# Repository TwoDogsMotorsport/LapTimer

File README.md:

# INFRARED LAP TIMER FOR CIRCUIT RACING

## INTRODUCTION

This is far from an original idea, but that doesn't mean you shouldn't have a go.

We take part in private track days as well as club sprint races, where the result is based on individual lap times rather than track position.

The benefit here is that you can tailor this system to suit your needs.  Want to store more laps, add a bigger display allow downloads?  All these things are possible.

While this looks a fair bit like the AIM or Motec displays, it is not compatible with them, and if we've done our homework properly our system and theirs happily ignore each other.  If not, please raise an issue.

## CAN I BUILD THIS?

If you have some basic electronics skill and can work with hand tools, I think that's all you need.  I will leave the packaging up to you because everyone's needs are different, but it is pretty simple to get going

## SHOPPING LIST

### TRANSMITTER

* 1 x Arduino Nano
* 1 x 940nm Infra Red LED
* 1 x 180 ohm 1/4W resistor

For a longer range unit, you can use multiple LEDs and an N-Channel MOSFET to drive them  Look at https://learn.adafruit.com/rgb-led-strips/usage for an example.  The included schematic shows four LEDs using a MOSFET, but you could run more (or less) if you want.

### RECEIVER

* 1 x Arduino Nano
* 1 x TSOP382 (or equivalent) Infra Red Receiver module
* 1 x 4-line x 20 character LCD display

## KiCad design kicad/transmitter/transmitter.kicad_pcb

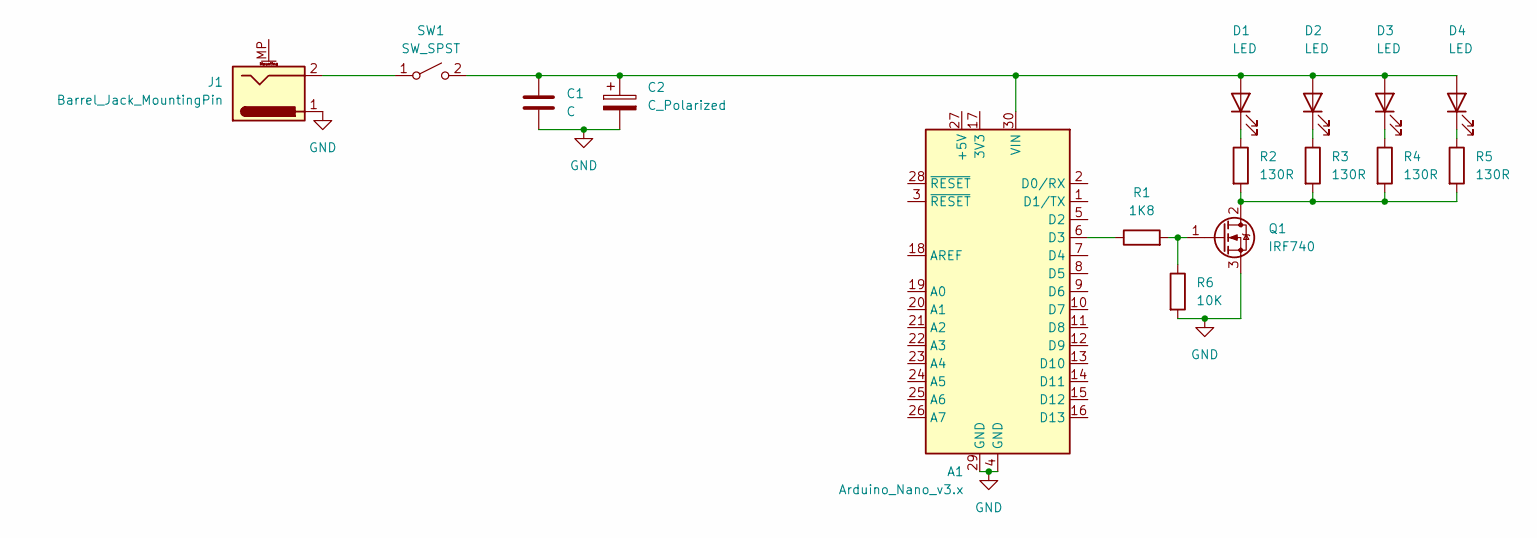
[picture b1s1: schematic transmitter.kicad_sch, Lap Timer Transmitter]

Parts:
A1: Arduino_Nano_v3.x; Arduino_Nano
C1: C; C_Disc_D4.7mm_W2.5mm_P5.00mm
C2: C_Polarized; CP_Radial_D10.0mm_P3.50mm
D1, D2, D3, D4: LED; LED_D5.0mm
J1: Barrel_Jack_MountingPin; BarrelJack_CUI_PJ-063AH_Horizontal
Q1: IRF740; TO-220-3_Vertical
R1: 1K8; R_Axial_DIN0207_L6.3mm_D2.5mm_P7.62mm_Horizontal
R2, R3, R4, R5: 130R; R_Axial_DIN0207_L6.3mm_D2.5mm_P7.62mm_Horizontal
R6: 10K; R_Axial_DIN0207_L6.3mm_D2.5mm_P7.62mm_Horizontal
SW1: SW_SPST; SW_Slide_SPDT_Straight_CK_OS102011MS2Q

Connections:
GND: A1.4 (GND), A1.29 (GND), C1.2, C2.2, J1.1, Q1.3 (S), R6.2
unnamed: A1.6 (D3), R1.1
unnamed: A1.30 (VIN), C1.1, C2.1, D1.2 (A), D2.2 (A), D3.2 (A), D4.2 (A), SW1.2 (B)
unnamed: D1.1 (K), R2.1
unnamed: D2.1 (K), R3.1
unnamed: D3.1 (K), R4.1
unnamed: D4.1 (K), R5.1
unnamed: Q1.2 (D), R2.2, R3.2, R4.2, R5.2
unnamed: Q1.1 (G), R1.2, R6.1
unnamed: J1.2, SW1.1 (A)

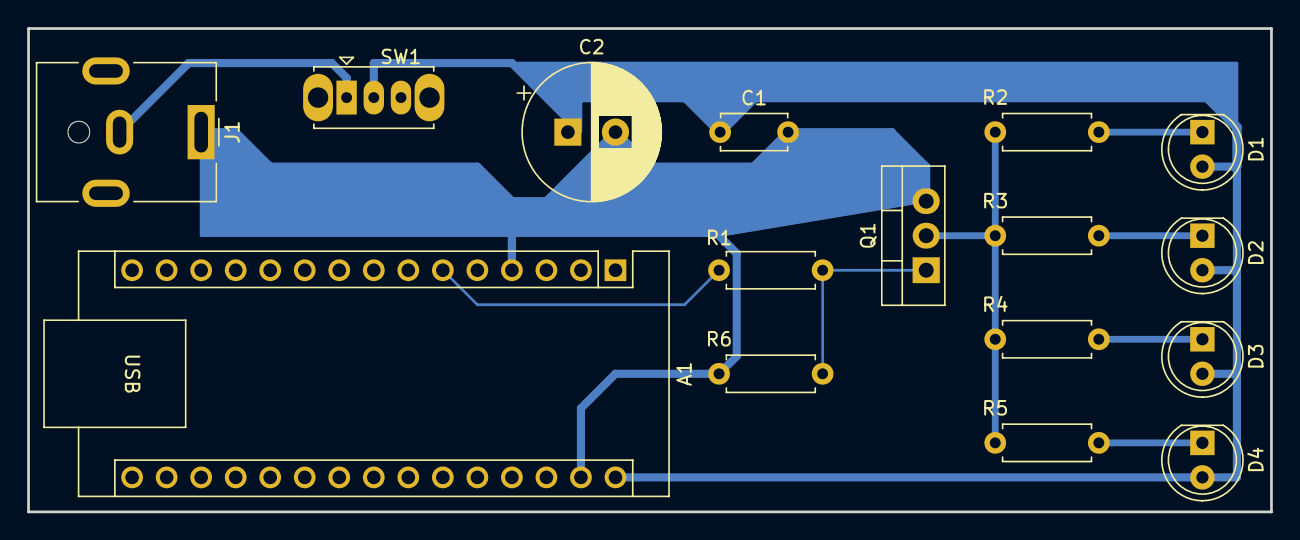
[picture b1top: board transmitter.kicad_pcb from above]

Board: 2 copper layers, 91.4 x 35.6 mm, 16 parts (0 on the bottom side), 10 nets.
